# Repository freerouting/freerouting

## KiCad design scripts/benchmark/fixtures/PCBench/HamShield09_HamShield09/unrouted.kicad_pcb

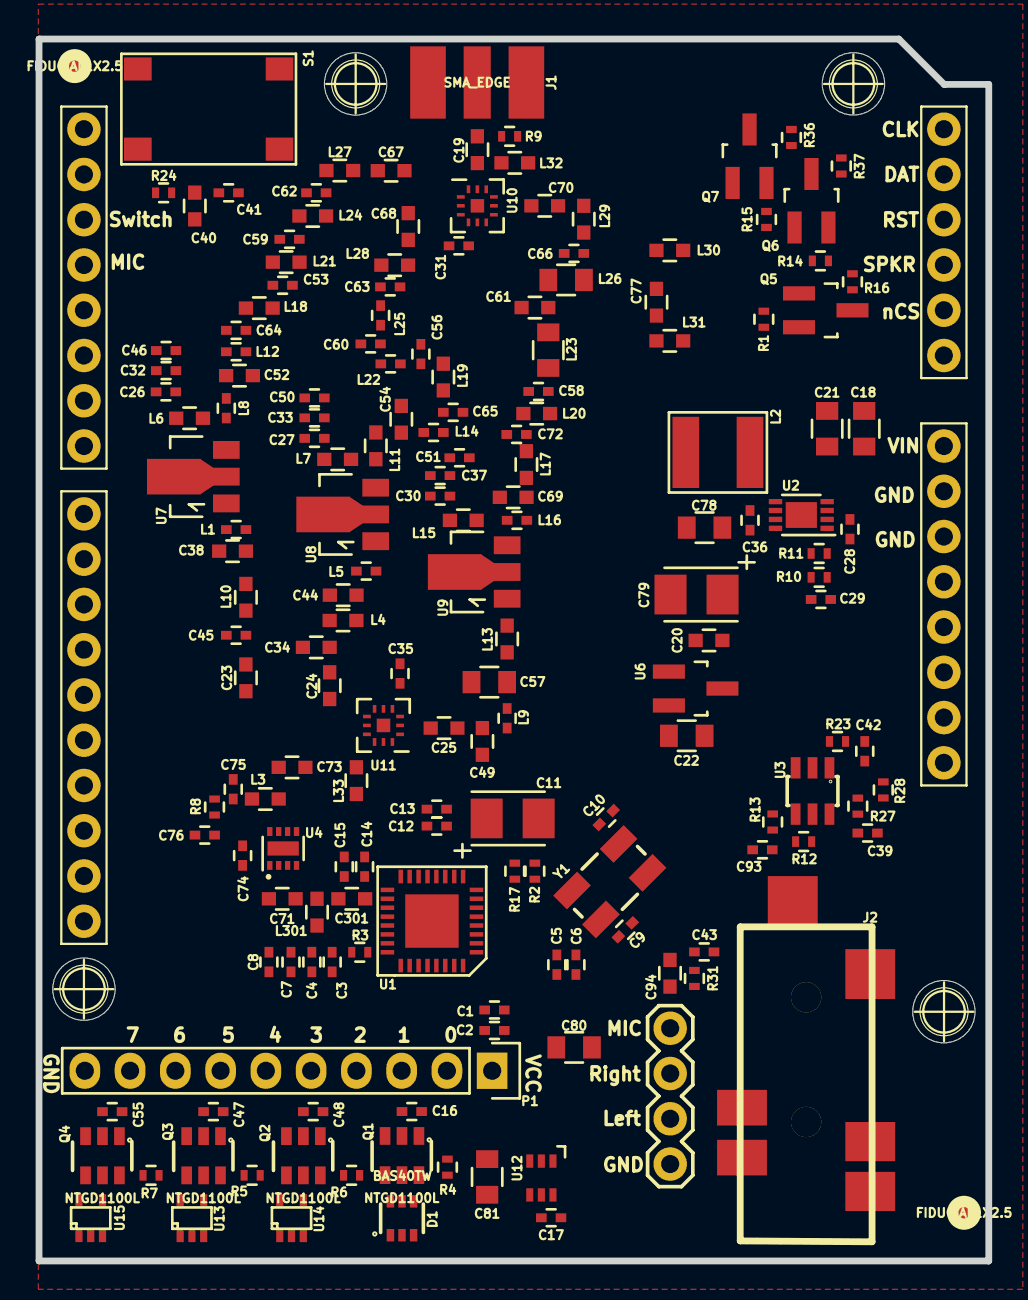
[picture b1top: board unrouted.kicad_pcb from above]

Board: 4 copper layers, 53.3 x 68.6 mm, 173 parts (0 on the bottom side), 100 nets, no tracks yet.

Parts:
C1, C3, C5, C7, C12, C14, C26, C27, C30, C41: 1n; C_0402
C2, C4, C6, C8, C16, C17, C31, C32, C33, C35, C36, C37, C39, C42, C43, C47, C48, C55, C74, C75, C76, C93: 0u1; C_0402
C9, C10, C15, C64: 10p; C_0402
C11, C79: 47u; C1210P
C13, C28, C29, C46, C50, C51: 1u; C_0402
C18, C21, C22, C78, C80: 10u; C_0805
C19, C23, C24, C25, C44, C67, C68, C70, C71, C73, C77: 100p; C_0603
C20: 4.7u; C_0603
C34, C52, C61: 24p; C_0603
C38: 56p; C_0603
C40, C94: 2u2; C_0603
C45, C60, C65: 15p; C_0402
C49, C54: 43p; C_0603
C53, C62: 7p; C_0402
C56, C63: 14p; C_0402
C57: 180p; C_0805
C58, C66: 20p; C_0402
C59: 8.2p; C_0402
C69: 68p; C_0603
C72: 27p; C_0402
C81: 22u; C_0805
C301: DNP; C_0603
D1: BAS40TW; SOT-363
FD1, FD2: FIDUCIAL1X2.5; SparkFun-FIDUCIAL-1X2.5
J1: SMA_EDGE; SMA-EDGE-HandSolder
J2: SJ-43514-SMT-TR
JP3: M04PTH; SparkFun-1X04
L1: 1ohm; C_0402
L2: NR5040T220M; NR5040
L3, L32, L33: 220n; C_0603
L4: 15n; C_0603
L5, L8: 3.6n; C_0402
L6, L7, L15: 100n; C_0603
L9: 24n; C_0402
L10, L13: 5.6n; C_0603
L11: 6.2n; C_0603
L12, L16: 12n; C_0402
L14: 18n; C_0402
L17, L21, L24: 33n; C_0603
L18, L27: 24n; C_0603
L19, L28: 47n; C_0603
L20, L29: 82n; C_0603
L22, L25: 75n; C_0402
L23, L26: 120n; C_0805
L30, L31, L301: DNP; C_0603
P1: CONN_01X10; Pin_Header_Straight_1x10
Q1, Q2, Q3, Q4: NTGD1100L; SC-74
Q5, Q6, Q7: BSS138; SOT-23_Handsoldering
R1, R4, R5, R6, R7, R9, R11, R14, R15, R16, R36, R37: 10k; R_0402
R2, R3, R13: 0; R_0402
R8: 1.8; R_0402
R10: 52.3k; R_0402
R12: dnp; R_0402
R17: DNP; R_0402
R23: 13.3; R_0402
R24: 20k; R_0402
R27, R28: 100k; R_0402
R31: 2k; R_0402
S1: TAC_SWITCHSMD; SWITCH_TACTILE_SMD_8mmX5mm
U1: AU1846; QFN32-5x5
U2: MCP16311; DFN-8-1EP_3x2mm_Pitch0.5mm
U3: AD8591; SOT23-6
U4: TRF37A75; DFN-8-1EP_2x2mm_Pitch0.5mm
U5: ARDUINO_SHIELD; ARDUINO_UNO_SHIELD
U6: AP2125N-3.3TRG1; SOT-23_Handsoldering
U7, U8, U9: TQP7M9105; SOT89-3_Housing
U10, U11: SKY13388; QFN-12-2mm-x-2mm
U12: NC7WZ14; SC-70-6
U13, U14, U15: NC7SZ08; sc70-5
Y1: 12.8MHz; SparkFun-CRYSTAL-SMD-5X3

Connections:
+5V: C20.1, C29.2, C31.1, C35.1, C78.2, C79.1, C81.2, L2.2, Q1.4, Q2.4, Q3.4, Q4.4, R4.1, R5.1, R6.1, R7.1, R10.1, U6.3, U10.3, U10.4, U11.3, U11.4
+5VL: R16.2, R36.2, R37.2, U5.5V
/GPIO0: P1.2, U1.32
/GPIO1: P1.3, U1.31
/GPIO2: P1.4, U1.30
/GPIO3: P1.5, U1.29
/GPIO6: P1.8, U1.26
/GPIO7: P1.9, U1.25
/Power Control/V1: D1.1, P1.6, U1.28, U11.5, U12.1, U13.1, U15.1
/Power Control/V2: D1.2, P1.7, U1.27, U11.6, U12.3, U14.2, U15.2
/Power Control/Y1: U10.5, U12.6, U14.1
/Power Control/Y2: U10.6, U12.4, U13.2
/Power Control/nRST: U2.3, U5.A3
/RF Front End/1.2m_IN: C24.1, U11.8
/RF Front End/1.2m_OUT: C68.1, U10.2
/RF Front End/2m_IN: C25.1, U11.2
/RF Front End/2m_OUT: C70.1, U10.8
/RF Front End/70cm_IN: C23.1, U11.9
/RF Front End/70cm_OUT: C67.1, U10.1
/RF Front End/ANT: C19.1, L32.2, U10.11
/RF Front End/RF_IN: C77.1, L31.1, U1.15
/RF Front End/RF_OUT: C71.2, C301.1, C301.2, L301.2, U1.18
/RF Front End/STAGE1_OUT: C73.1, L33.2, U11.11
/User Interface/AFOUT: U1.9, U3.3
/User Interface/ARD_AUDIO_OUT: C42.2, R27.1, R28.1, U5.A2
/User Interface/MIC_IN: C40.1, C94.1, U1.11
/User Interface/MODE: R2.1, R17.1, U1.7
/User Interface/PDN: R3.1, U1.24
/User Interface/PWM_AUDIO_IN: R24.2, U5.D3
/User Interface/SCLK: Q7.2, R15.1, U1.2
/User Interface/SDIO: Q6.2, R14.1, U1.3
/User Interface/nSEN: Q5.2, R1.1, U1.8
AVDD: C18.1, C21.1, U2.4, U5.VIN
GND: C1.2, C2.2, C3.2, C4.2, C5.2, C6.2, C7.2, C8.2, C9.2, C10.2, C11.2, C12.2, C13.2, C14.2, C15.2, C16.2, C17.1, C18.2, C20.2, C21.2, C22.1, C26.2, C27.2, C28.2, C29.1, C30.2, C31.2, C32.2, C33.2, C34.2, C35.2, C37.2, C38.2, C39.1, C41.1, C43.1, C44.2, C45.2, C46.2, C47.2, C48.2, C49.2, C50.2, C51.2, C52.2, C53.2, C54.2, C55.2, C56.2, C57.2, C58.2, C59.2, C60.2, C61.2, C62.2, C63.2, C64.2, C65.2, C66.2, C69.2, C72.2, C74.2, C75.2, C76.2, C78.1, C79.2, C80.1, C81.1, D1.3, J1.GND, J2.4, JP3.4, L30.2, L31.2, L32.1, L33.1, L301.1, P1.10, Q1.1, Q2.1, Q3.1, Q4.1, R9.2, R11.2, R12.1, R17.2, R28.2, S1.3, S1.4, U2.5, U2.8, U2.9, U3.2, U4.3, U4.4, U4.5, U4.6, U4.8, U4.9, U5.GP1, U5.GP2, U6.1, U7.2, U8.2, U9.2, U10.7, U10.10, U10.12, U10.13, U11.7, U11.10, U11.12, U11.13, U12.2, U13.3, U14.3, U15.3, Y1.2, Y1.4
unnamed: C9.1, U1.5, Y1.1
unnamed: C10.1, U1.6, Y1.3
unnamed: C11.1, U1.12
unnamed: C19.2, J1.SIG, R9.1
unnamed: C23.2, C45.1, L10.1
unnamed: C24.2, C34.1, L4.1
unnamed: C25.2, C49.1, L9.1
unnamed: C28.1, U2.2
unnamed: C36.1, U2.7
unnamed: C36.2, L2.1, U2.6
unnamed: C38.1, L1.1, L10.2
unnamed: C40.2, C41.2, R24.1
unnamed: C42.1, C93.1, R13.2, R23.2
unnamed: C44.1, L4.2, L5.1
unnamed: C52.1, L8.1, L12.2
unnamed: C53.1, L18.1, L21.2
unnamed: C54.1, L11.1, L14.2
unnamed: C56.1, L19.1, L22.2
unnamed: C57.1, L9.2, L13.1
unnamed: C58.1, L20.1, L23.2
unnamed: C59.1, L21.1, L24.2
unnamed: C60.1, L22.1, L25.2
unnamed: C61.1, L23.1, L26.2
unnamed: C62.1, L24.1, L27.2
unnamed: C63.1, L25.1, L28.2
unnamed: C64.1, L12.1, L18.2
unnamed: C65.1, L14.1, L19.2
unnamed: C66.1, L26.1, L29.2
unnamed: C67.2, L27.1
unnamed: C68.2, L28.1
unnamed: C69.1, L16.1, L17.2
unnamed: C70.2, L29.1
unnamed: C71.1, U4.2
unnamed: C72.1, L17.1, L20.2
unnamed: C73.2, L3.1, U4.7
unnamed: C75.1, L3.2, R8.1
unnamed: C77.2, L30.1, U10.9
unnamed: C93.2, J2.3, JP3.2
unnamed: C94.2, J2.1, JP3.1, R31.2
unnamed: D1.4, D1.5, D1.6, Q1.5
unnamed: J2.2, JP3.3
unnamed: L1.2, U7.1
unnamed: L5.2, U8.1
unnamed: L6.2, L8.2, U7.3
unnamed: L7.2, L11.2, U8.3
unnamed: L13.2, U9.1
unnamed: L15.2, L16.2, U9.3
unnamed: Q1.6, R4.2
unnamed: Q2.5, U14.4
unnamed: Q2.6, R6.2
unnamed: Q3.5, U13.4
unnamed: Q3.6, R5.2
unnamed: Q4.5, U15.4
unnamed: Q4.6, R7.2
unnamed: Q5.3, R16.1, U5.A1
unnamed: Q6.3, R37.1, U5.A4
unnamed: Q7.3, R36.1, U5.A5
unnamed: R10.2, R11.1, U2.1
unnamed: R12.2, R13.1, U3.4
unnamed: R23.1, U3.1
unnamed: S1.1, S1.2, U5.D2
VCC: C1.1, C2.1, C3.1, C4.1, C5.1, C6.1, C7.1, C8.1, C12.1, C13.1, C14.1, C15.1, C17.2, C22.2, C39.2, C80.2, P1.1, Q5.1, Q6.1, Q7.1, R1.2, R2.2, R3.2, R14.2, R15.2, R27.2, U1.1, U1.4, U1.13, U1.16, U1.21, U1.23, U3.5, U3.6, U6.2, U12.5, U13.5, U14.5, U15.5
VTX: C16.1, C43.2, C74.1, C76.1, Q1.2, Q1.3, R8.2, R31.1, U4.1
V_1.2M: C27.1, C33.1, C47.1, C50.1, L7.1, Q3.2, Q3.3
V_2M: C30.1, C37.1, C48.1, C51.1, L15.1, Q2.2, Q2.3
V_70CM: C26.1, C32.1, C46.1, C55.1, L6.1, Q4.2, Q4.3

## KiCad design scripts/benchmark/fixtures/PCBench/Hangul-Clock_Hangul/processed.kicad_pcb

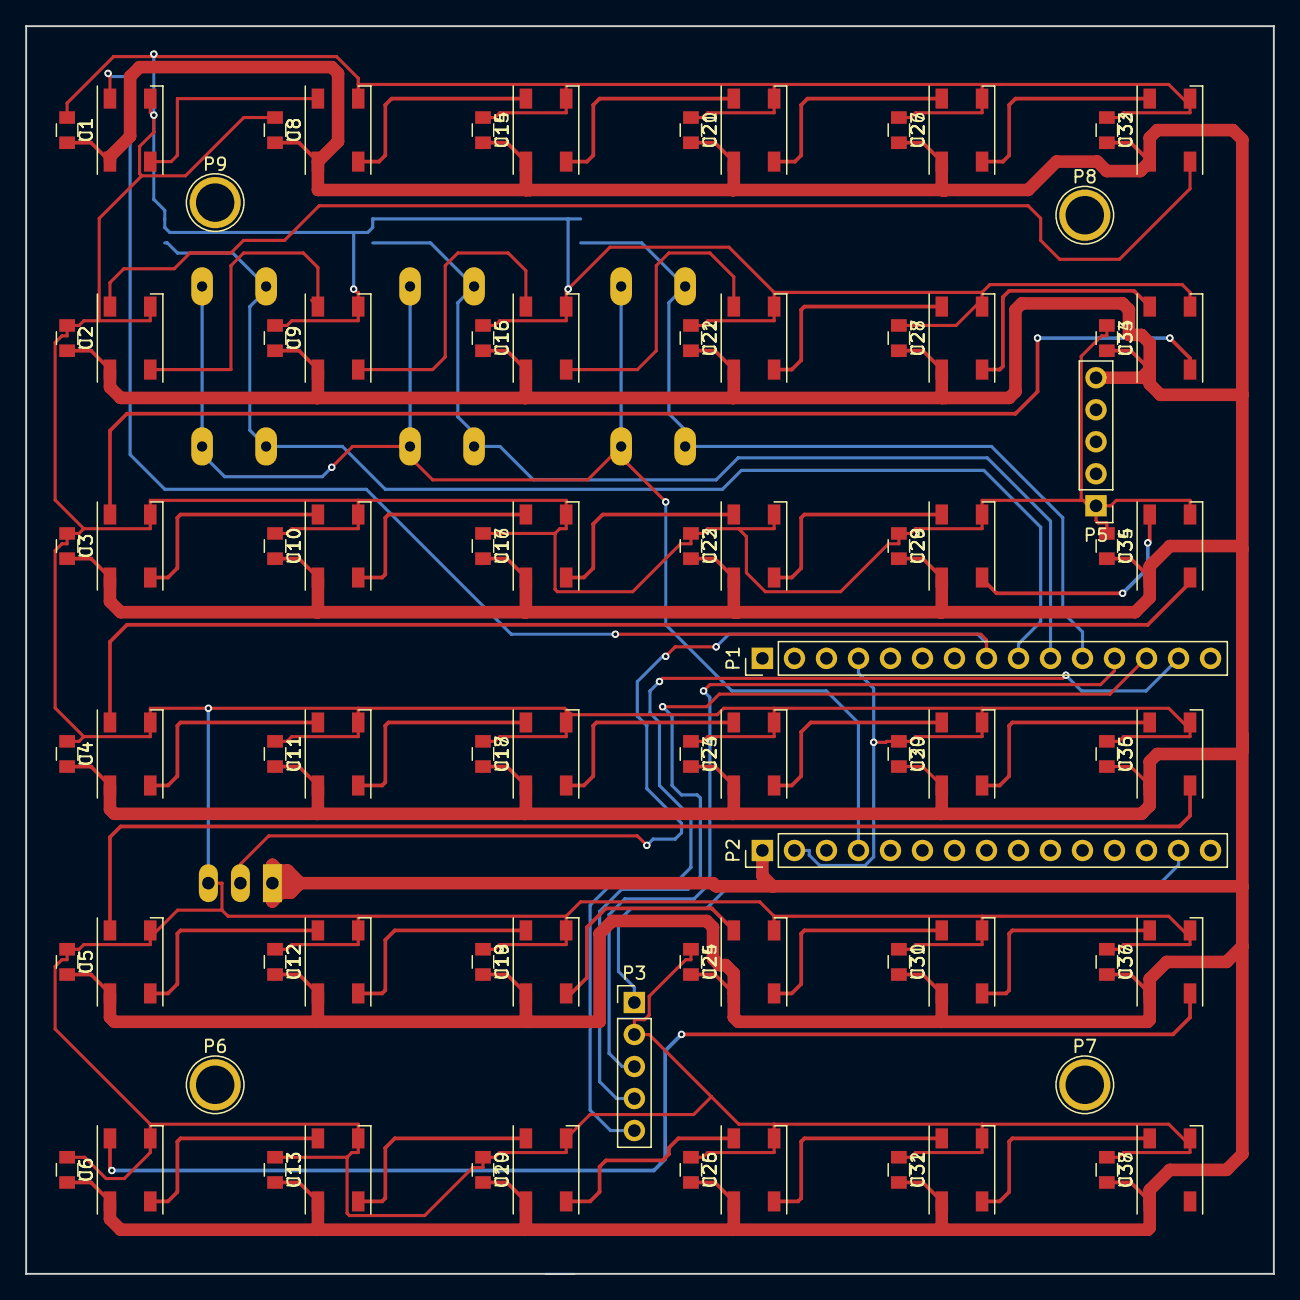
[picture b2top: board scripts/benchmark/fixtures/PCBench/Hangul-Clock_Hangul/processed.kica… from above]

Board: 2 copper layers, 99.0 x 99.0 mm, 87 parts (0 on the bottom side), 46 nets.

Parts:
C1, C2, C3, C4, C5, C6, C8, C9, C10, C11, C12, C13, C15, C16, C17, C18, C19, C20, C21, C22, C23, C24, C25, C26, C27, C28, C29, C30, C31, C32, C33, C34, C35, C36, C37, C38: C; C_0805
P1: NANO_1; Pin_Header_Straight_1x15_Pitch2.54mm
P2: NANO_2; Pin_Header_Straight_1x15_Pitch2.54mm
P3: DS1302; Pin_Header_Straight_1x05_Pitch2.54mm
P4: CONN_01X03; MOLEX-5045-03A
P5: POWER; Pin_Header_Straight_1x05_Pitch2.54mm
P6, P7, P8, P9: S; 1pin
R1, R2, R3: R; R_0805BCU
SW1: SW_R; SW_PUSH-12mmBCU
SW2: SW_G; SW_PUSH-12mmBCU
SW3: SW_B; SW_PUSH-12mmBCU
U1, U2, U3, U4, U5, U6, U8, U9, U10, U11, U12, U13, U14, U15, U16, U17, U18, U19, U20, U21, U22, U23, U24, U25, U26, U27, U28, U29, U30, U31, U32, U33, U34, U35, U36, U37: WS2812B; LED_WS2812B-PLCC4

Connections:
+5V: P2.4, SW1.1, SW2.1, SW3.1
+5VA: C1.2, C2.2, C3.2, C4.2, C5.2, C6.2, C8.2, C9.2, C10.2, C11.2, C12.2, C13.2, C15.2, C16.2, C17.2, C18.2, C19.2, C20.2, C21.2, C22.2, C23.2, C24.2, C25.2, C26.2, C27.2, C28.2, C29.2, C30.2, C31.2, C32.2, C33.2, C34.2, C35.2, C36.2, C37.2, C38.2, P2.1, P4.1, P5.5, U1.1, U2.1, U3.1, U4.1, U5.1, U6.1, U8.1, U9.1, U10.1, U11.1, U12.1, U13.1, U14.1, U15.1, U16.1, U17.1, U18.1, U19.1, U20.1, U21.1, U22.1, U23.1, U24.1, U25.1, U26.1, U27.1, U28.1, U29.1, U30.1, U31.1, U32.1, U33.1, U34.1, U35.1, U36.1, U37.1
CLK: P1.12, P3.3
DAT: P1.13, P3.4
DIN: P1.8, P4.2, U1.4
GND: C1.1, C2.1, C3.1, C4.1, C5.1, C6.1, C8.1, C9.1, C10.1, C11.1, C12.1, C13.1, C15.1, C16.1, C17.1, C18.1, C19.1, C20.1, C21.1, C22.1, C23.1, C24.1, C25.1, C26.1, C27.1, C28.1, C29.1, C30.1, C31.1, C32.1, C33.1, C34.1, C35.1, C36.1, C37.1, C38.1, P1.4, P2.2, P3.2, P4.3, P5.1, R1.1, R2.1, R3.1, U1.3, U2.3, U3.3, U4.3, U5.3, U6.3, U8.3, U9.3, U10.3, U11.3, U12.3, U13.3, U14.3, U15.3, U16.3, U17.3, U18.3, U19.3, U20.3, U21.3, U22.3, U23.3, U24.3, U25.3, U26.3, U27.3, U28.3, U29.3, U30.3, U31.3, U32.3, U33.3, U34.3, U35.3, U36.3, U37.3
unnamed: P1.9, R1.2, SW1.2
unnamed: P1.10, R2.2, SW2.2
unnamed: P1.11, R3.2, SW3.2
unnamed: P2.14, P3.1
unnamed: U1.2, U8.4
unnamed: U2.2, U9.4
unnamed: U2.4, U32.2
unnamed: U3.4, U33.2
unnamed: U10.2, U16.4
unnamed: U3.2, U10.4
unnamed: U11.2, U17.4
unnamed: U4.2, U11.4
unnamed: U12.2, U18.4
unnamed: U5.2, U12.4
unnamed: U13.2, U19.4
unnamed: U6.2, U13.4
unnamed: U14.2, U20.4
unnamed: U8.2, U14.4
unnamed: U15.2, U21.4
unnamed: U9.2, U15.4
unnamed: U16.2, U22.4
unnamed: U17.2, U23.4
unnamed: U18.2, U24.4
unnamed: U19.2, U25.4
unnamed: U20.2, U26.4
unnamed: U21.2, U27.4
unnamed: U22.2, U28.4
unnamed: U23.2, U29.4
unnamed: U24.2, U30.4
unnamed: U25.2, U31.4
unnamed: U26.2, U32.4
unnamed: U27.2, U33.4
unnamed: U28.2, U34.4
unnamed: U29.2, U35.4
unnamed: U30.2, U36.4
unnamed: U31.2, U37.4
unnamed: U4.4, U34.2
unnamed: U5.4, U35.2
unnamed: U6.4, U36.2
RST: P1.14, P3.5

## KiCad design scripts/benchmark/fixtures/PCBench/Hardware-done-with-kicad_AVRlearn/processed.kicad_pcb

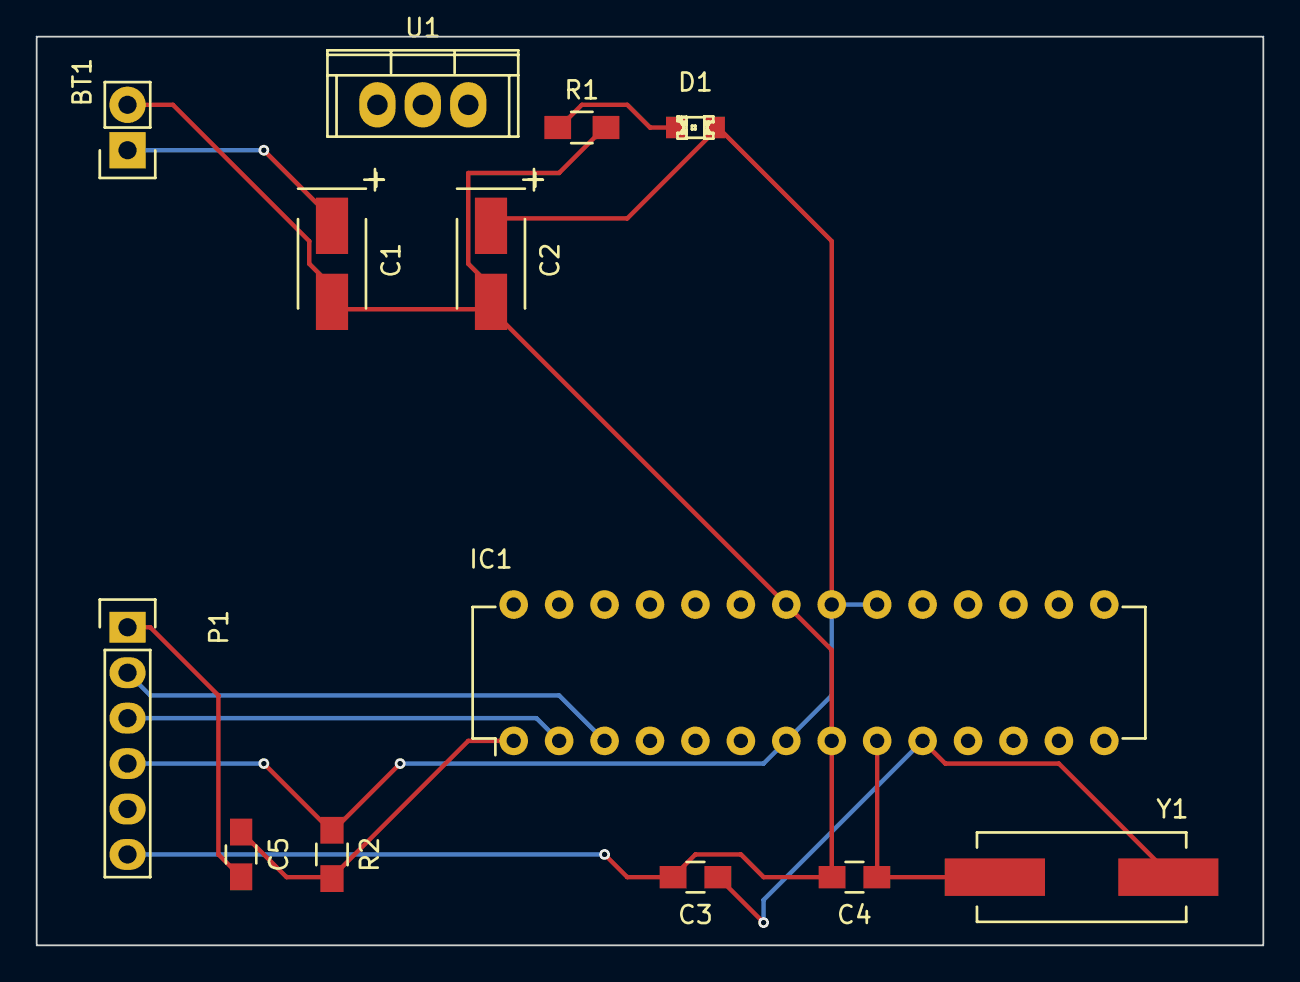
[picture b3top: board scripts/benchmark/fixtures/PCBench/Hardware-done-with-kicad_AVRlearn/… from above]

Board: 2 copper layers, 68.6 x 50.8 mm, 13 parts (0 on the bottom side), 10 nets.

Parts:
BT1: 9V; Socket_Strip_Straight_1x02
C1: 100uF; TantalC_SizeB_EIA-3528_HandSoldering
C2: 10uF; TantalC_SizeB_EIA-3528_HandSoldering
C3, C4: 22pF; C_0805_HandSoldering
C5: 0.1uF; C_0805_HandSoldering
D1: LED; LED-0805
IC1: ATMEGA328P-P; DIP-28_W7.62mm
P1: CONN_01X06; Socket_Strip_Straight_1x06
R1: 330R; R_0805_HandSoldering
R2: 10k; R_0805_HandSoldering
U1: LM7805; TO-220
Y1: 16MHz; Crystal_HC49-SD_SMD

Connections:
/DTR: C5.2, P1.1
/RX: IC1.2, P1.3
/TX: IC1.3, P1.2
GND: BT1.2, C1.2, C2.2, C3.2, C4.2, IC1.8, IC1.22, P1.6, R1.2
unnamed: BT1.1, C1.1
unnamed: C3.1, IC1.10, Y1.1
unnamed: C4.1, IC1.9, Y1.2
unnamed: C5.1, IC1.1, R2.2
unnamed: D1.1, R1.1
VCC: C2.1, D1.2, IC1.7, IC1.20, IC1.21, P1.4, R2.1

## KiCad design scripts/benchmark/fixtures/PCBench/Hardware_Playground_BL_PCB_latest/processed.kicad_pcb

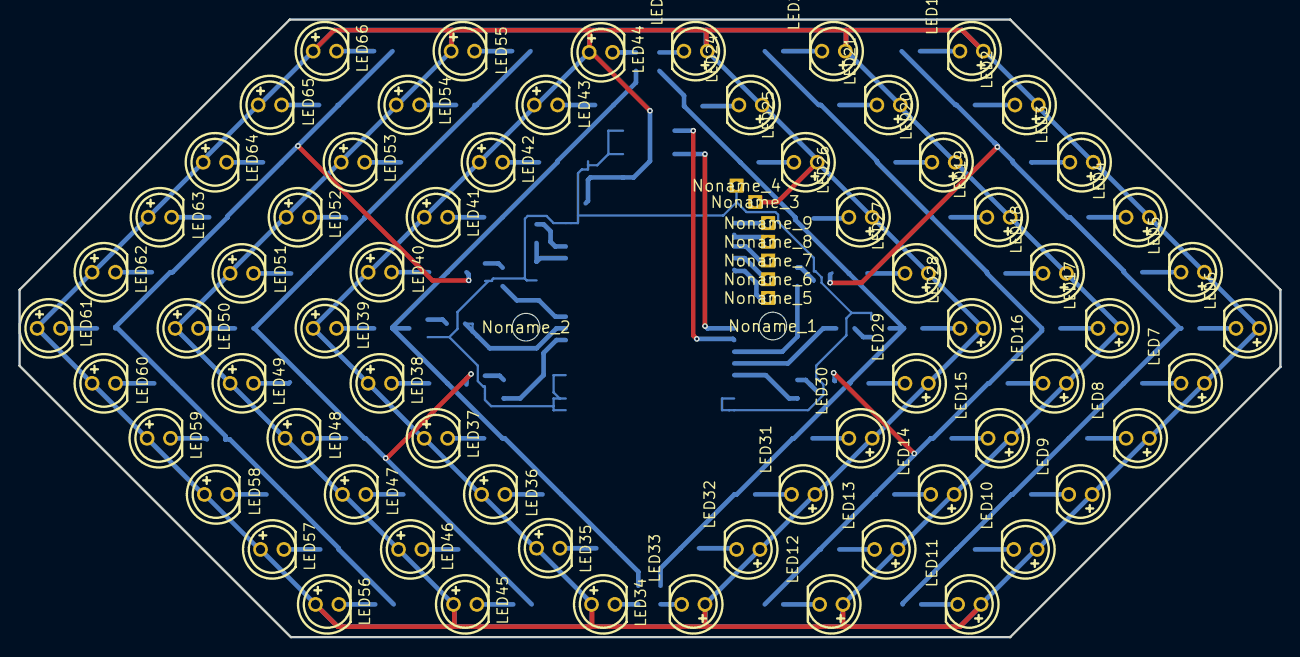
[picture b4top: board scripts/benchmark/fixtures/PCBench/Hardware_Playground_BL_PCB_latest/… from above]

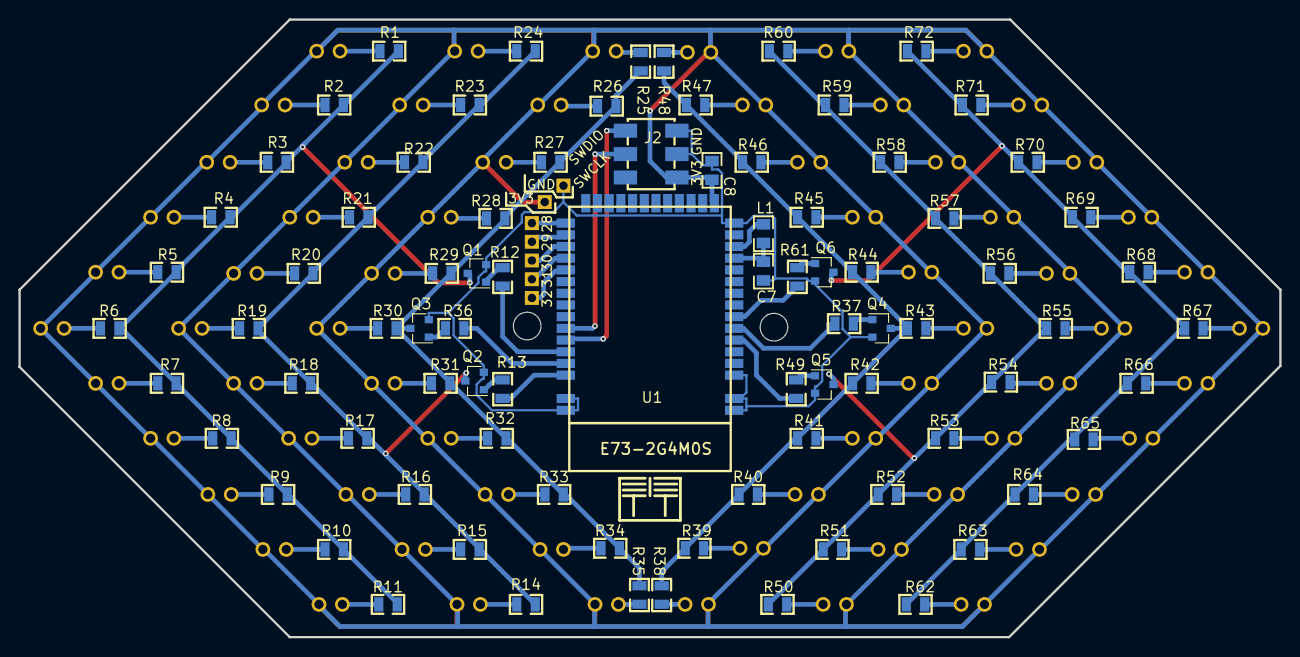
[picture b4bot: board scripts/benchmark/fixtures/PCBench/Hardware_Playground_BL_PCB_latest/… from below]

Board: 2 copper layers, 136.9 x 67.1 mm, 159 parts (6 on the bottom side), 95 nets.

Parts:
C7: 1u; 0805
C8: 10u; 0805
J2: SWD; H2X3-SMD-2.54
L1: 10uH; 0805
LED1, LED2, LED3, LED4, LED5, LED6, LED7, LED8, LED9, LED10, LED11, LED12, LED13, LED14, LED15, LED16, LED17, LED18, LED19, LED20, LED21, LED22, LED23, LED24, LED25, LED26, LED27, LED28, LED29, LED30, LED31, LED32, LED33, LED34, LED35, LED36, LED37, LED38, LED39, LED40, LED41, LED42, LED43, LED44, LED45, LED46, LED47, LED48, LED49, LED50, LED51, LED52, LED53, LED54, LED55, LED56, LED57, LED58, LED59, LED60, LED61, LED62, LED63, LED64, LED65, LED66: HL-503S45FC; LED-TH_BD5.0-P2.54-FD
LG: my_logo; ggeac4e8891367b2b2c
Noname_1, Noname_2: MountingHole_3.00mm
Noname_3, Noname_4, Noname_5, Noname_6, Noname_7, Noname_8, Noname_9: Pad_1.52mm
Q1, Q2, Q3, Q4, Q5, Q6: MMBT2222; SOT-23
R1, R2, R3, R4, R5, R6, R7, R8, R9, R10, R11, R14, R15, R16, R17, R18, R19, R20, R21, R22, R23, R24, R25, R26, R27, R28, R29, R30, R31, R32, R33, R34, R35, R38, R39, R40, R41, R42, R43, R44, R45, R46, R47, R48, R50, R51, R52, R53, R54, R55, R56, R57, R58, R59, R60, R62, R63, R64, R65, R66, R67, R68, R69, R70, R71, R72: 33; R0805
R12, R13, R36, R37, R49, R61: 1K; R0805
U1: E73-2G4M0S; E73-2G4M04S

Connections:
+3V3: C8.2, J2.1, LED1.1, LED2.1, LED3.1, LED4.1, LED5.1, LED6.1, LED7.1, LED8.1, LED9.1, LED10.1, LED11.1, LED12.1, LED13.1, LED14.1, LED15.1, LED16.1, LED17.1, LED18.1, LED19.1, LED20.1, LED21.1, LED22.1, LED23.1, LED24.1, LED25.1, LED26.1, LED27.1, LED28.1, LED29.1, LED30.1, LED31.1, LED32.1, LED33.1, LED34.1, LED35.1, LED36.1, LED37.1, LED38.1, LED39.1, LED40.1, LED41.1, LED42.1, LED43.1, LED44.1, LED45.1, LED46.1, LED47.1, LED48.1, LED49.1, LED50.1, LED51.1, LED52.1, LED53.1, LED54.1, LED55.1, LED56.1, LED57.1, LED58.1, LED59.1, LED60.1, LED61.1, LED62.1, LED63.1, LED64.1, LED65.1, LED66.1, Noname_3.3, U1.16
AL1: R12.1, U1.39
AL2: R13.1, U1.41
AL3: R36.1, U1.40
AR1: R37.1, U1.6
AR2: R49.1, U1.5
AR3: R61.1, U1.7
C7_2: C7.2, L1.1, U1.12
GND: C7.1, C8.1, J2.2, J2.3, Noname_4.2, Q1.2, Q2.2, Q3.2, Q4.2, Q5.2, Q6.2, U1.0, U1.1, U1.2, U1.15, U1.42, U1.43
L1_2: L1.2, U1.13
LED1_2: LED1.2, R1.2
LED2_2: LED2.2, R2.2
LED3_2: LED3.2, R3.2
LED4_2: LED4.2, R4.2
LED5_2: LED5.2, R5.2
LED6_2: LED6.2, R6.2
LED7_2: LED7.2, R7.2
LED8_2: LED8.2, R8.2
LED9_2: LED9.2, R9.2
LED10_2: LED10.2, R10.2
LED11_2: LED11.2, R11.2
LED23_2: LED23.2, R25.2
LED24_2: LED24.2, R26.2
LED25_2: LED25.2, R27.2
LED26_2: LED26.2, R28.2
LED27_2: LED27.2, R29.2
LED28_2: LED28.2, R30.2
LED29_2: LED29.2, R31.2
LED30_2: LED30.2, R32.2
LED31_2: LED31.2, R33.2
LED32_2: LED32.2, R34.2
LED33_2: LED33.2, R35.2
unnamed: Noname_9.1, U1.28
unnamed: Noname_8.1, U1.29
unnamed: Noname_7.1, U1.30
unnamed: Noname_6.1, U1.31
unnamed: Noname_5.1, U1.32
Q1_1: Q1.1, R12.2
Q2_3: Q2.3, R14.1, R15.1, R16.1, R17.1, R18.1, R19.1, R20.1, R21.1, R22.1, R23.1, R24.1
Q3_1: Q3.1, R36.2
Q4_3: Q4.3, R38.1, R39.1, R40.1, R41.1, R42.1, R43.1, R44.1, R45.1, R46.1, R47.1, R48.1
Q5_3: Q5.3, R50.1, R51.1, R52.1, R53.1, R54.1, R55.1, R56.1, R57.1, R58.1, R59.1, R60.1
Q6_3: Q6.3, R62.1, R63.1, R64.1, R65.1, R66.1, R67.1, R68.1, R69.1, R70.1, R71.1, R72.1
R1_1: Q1.3, R1.1, R2.1, R3.1, R4.1, R5.1, R6.1, R7.1, R8.1, R9.1, R10.1, R11.1
R13_2: Q2.1, R13.2
R14_2: LED12.2, R14.2
R15_2: LED13.2, R15.2
R16_2: LED14.2, R16.2
R17_2: LED15.2, R17.2
R18_2: LED16.2, R18.2
R19_2: LED17.2, R19.2
R20_2: LED18.2, R20.2
R21_2: LED19.2, R21.2
R22_2: LED20.2, R22.2
R23_2: LED21.2, R23.2
R24_2: LED22.2, R24.2
R25_1: Q3.3, R25.1, R26.1, R27.1, R28.1, R29.1, R30.1, R31.1, R32.1, R33.1, R34.1, R35.1
R37_2: Q4.1, R37.2
R38_2: LED34.2, R38.2
R39_2: LED35.2, R39.2
R40_2: LED36.2, R40.2
R41_2: LED37.2, R41.2
R42_2: LED38.2, R42.2
R43_2: LED39.2, R43.2
R44_2: LED40.2, R44.2
R45_2: LED41.2, R45.2
R46_2: LED42.2, R46.2
R47_2: LED43.2, R47.2
R48_2: LED44.2, R48.2
R49_2: Q5.1, R49.2
R50_2: LED45.2, R50.2
R51_2: LED46.2, R51.2
R52_2: LED47.2, R52.2
R53_2: LED48.2, R53.2
R54_2: LED49.2, R54.2
R55_2: LED50.2, R55.2
R56_2: LED51.2, R56.2
R57_2: LED52.2, R57.2
R58_2: LED53.2, R58.2
R59_2: LED54.2, R59.2
R60_2: LED55.2, R60.2
R61_2: Q6.1, R61.2
R62_2: LED56.2, R62.2
R63_2: LED57.2, R63.2
R64_2: LED58.2, R64.2
R65_2: LED59.2, R65.2
R66_2: LED60.2, R66.2
R67_2: LED61.2, R67.2
R68_2: LED62.2, R68.2
R69_2: LED63.2, R69.2
R70_2: LED64.2, R70.2
R71_2: LED65.2, R71.2
R72_2: LED66.2, R72.2
SWCLK: J2.5, U1.37
SWDIO: J2.4, U1.38
